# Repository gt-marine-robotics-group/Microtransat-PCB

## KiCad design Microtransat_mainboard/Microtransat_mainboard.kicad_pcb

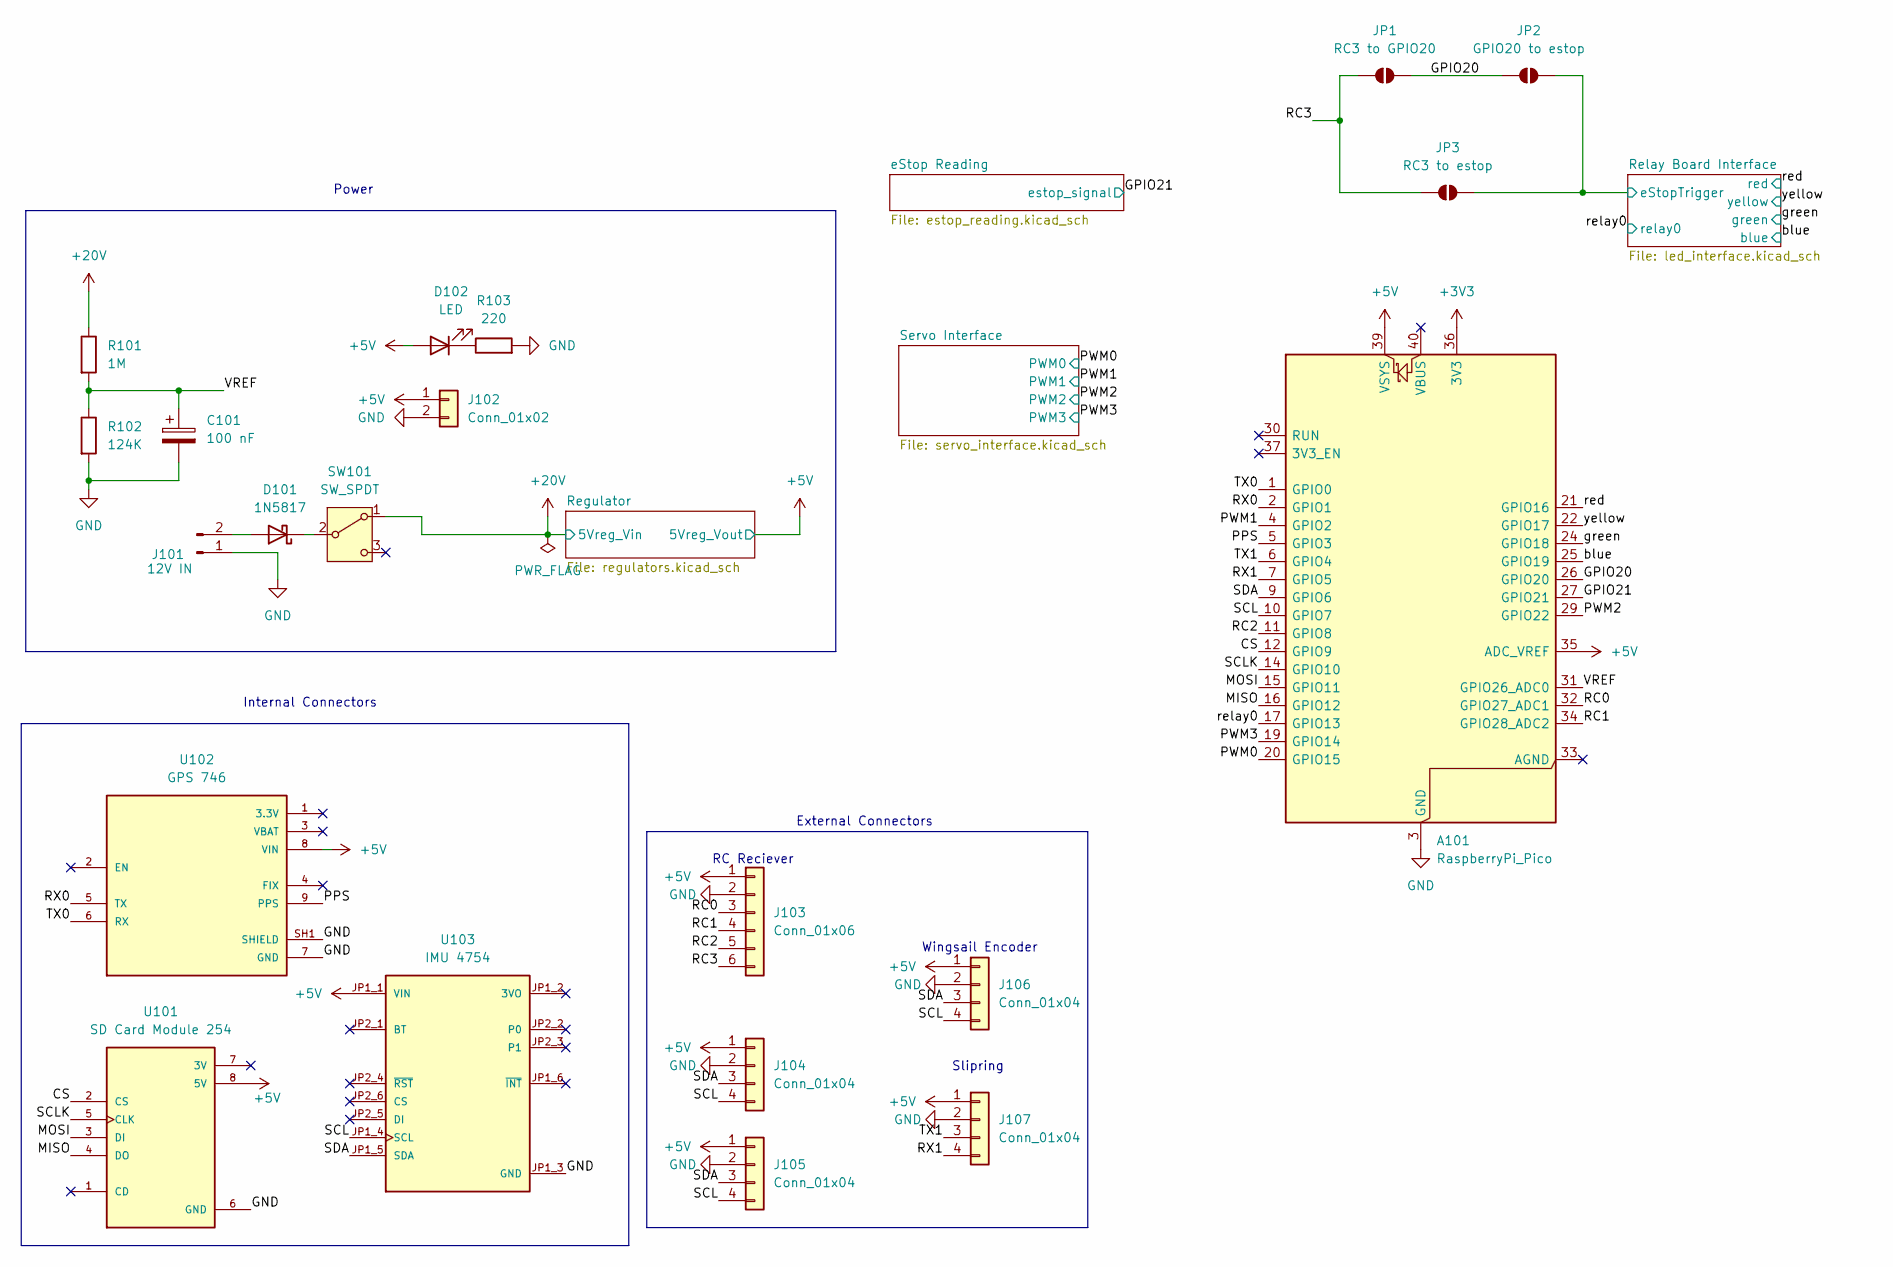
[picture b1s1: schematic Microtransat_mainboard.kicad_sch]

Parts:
A101: RaspberryPi_Pico; RaspberryPi_Pico_Common_Unspecified
C101: 100 nF; C_1206_3216Metric_Pad1.33x1.80mm_HandSolder
D101: 1N5817; D_DO-41_SOD81_P10.16mm_Horizontal
D102: LED; LED_1206_3216Metric_Pad1.42x1.75mm_HandSolder
J101: 12V IN; AMASS_XT30PW-M_1x02_P2.50mm_Horizontal
J102: Conn_01x02; JST_XH_B2B-XH-A_1x02_P2.50mm_Vertical
J103: Conn_01x06; JST_XH_B6B-XH-A_1x06_P2.50mm_Vertical
J104, J105, J106, J107: Conn_01x04; JST_XH_B4B-XH-A_1x04_P2.50mm_Vertical
JP1: RC3 to GPIO20; SolderJumper-2_P1.3mm_Open_RoundedPad1.0x1.5mm
JP2: GPIO20 to estop; SolderJumper-2_P1.3mm_Open_RoundedPad1.0x1.5mm
JP3: RC3 to estop; SolderJumper-2_P1.3mm_Open_RoundedPad1.0x1.5mm
R101: 1M; R_1206_3216Metric_Pad1.30x1.75mm_HandSolder
R102: 124K; R_1206_3216Metric_Pad1.30x1.75mm_HandSolder
R103: 220; R_1206_3216Metric_Pad1.30x1.75mm_HandSolder
SW101: SW_SPDT; SW_EG1218
U101: SD Card Module 254; MODULE_254; PARTREV Jul 31, 2013; DigiKey_Part_Number 1528-1462-ND
U102: GPS 746; XCVR_746; PARTREV 2022-12-01; DigiKey_Part_Number 1528-1153-ND
U103: IMU 4754; MODULE_4754; PARTREV 2021-03-16; DigiKey_Part_Number 1528-4754-ND

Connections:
+3V3: A101.36 (3V3); also elsewhere on the board
+5V: A101.35 (ADC_VREF), A101.39 (VSYS), D102.2 (A), J102.1, J103.1, J104.1, J105.1, J106.1, J107.1, U101.8 (5V), U102.8 (VIN), U103.JP1_1 (VIN); also elsewhere on the board
+20V: R101.1, SW101.1 (A); also elsewhere on the board
/CS: A101.12 (GPIO9), U101.2 (CS)
/GPIO20: A101.26 (GPIO20), JP1.2 (B), JP2.1 (A)
/GPIO21: A101.27 (GPIO21); also elsewhere on the board
/MISO: A101.16 (GPIO12), U101.4 (DO)
/MOSI: A101.15 (GPIO11), U101.3 (DI)
/PPS: A101.5 (GPIO3), U102.9 (PPS)
/PWM0: A101.20 (GPIO15); also elsewhere on the board
/PWM1: A101.4 (GPIO2); also elsewhere on the board
/PWM2: A101.29 (GPIO22); also elsewhere on the board
/PWM3: A101.19 (GPIO14); also elsewhere on the board
/RC0: A101.32 (GPIO27_ADC1), J103.3
/RC1: A101.34 (GPIO28_ADC2), J103.4
/RC2: A101.11 (GPIO8), J103.5
/RC3: J103.6, JP1.1 (A), JP3.1 (A)
/RX0: A101.2 (GPIO1), U102.5 (TX)
/RX1: A101.7 (GPIO5), J107.4
/Relay Board Interface/eStopTrigger: JP2.2 (B), JP3.2 (B); also elsewhere on the board
/SCL: A101.10 (GPIO7), J104.4, J105.4, J106.4, U103.JP1_4 (SCL)
/SCLK: A101.14 (GPIO10), U101.5 (CLK)
/SDA: A101.9 (GPIO6), J104.3, J105.3, J106.3, U103.JP1_5 (SDA)
/TX0: A101.1 (GPIO0), U102.6 (RX)
/TX1: A101.6 (GPIO4), J107.3
/VREF: A101.31 (GPIO26_ADC0), C101.1, R101.2, R102.1
/blue: A101.25 (GPIO19); also elsewhere on the board
/green: A101.24 (GPIO18); also elsewhere on the board
/red: A101.21 (GPIO16); also elsewhere on the board
/relay0: A101.17 (GPIO13); also elsewhere on the board
/yellow: A101.22 (GPIO17); also elsewhere on the board
GND: A101.3 (GND), A101.8 (GND), A101.13 (GND), A101.18 (GND), A101.23 (GND), A101.28 (GND), A101.38 (GND), C101.2, J101.1, J102.2, J103.2, J104.2, J105.2, J106.2, J107.2, R102.2, R103.2, U101.6 (GND), U102.7 (GND), U102.SH1 (SHIELD), U102.SH2 (SHIELD), U103.JP1_3 (GND); also elsewhere on the board
unnamed: D101.2 (A), J101.2
unnamed: D101.1 (K), SW101.2 (B)
unnamed: D102.1 (K), R103.1

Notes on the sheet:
Wingsail Encoder
Internal Connectors
Power
Slipring
RC Reciever
External Connectors

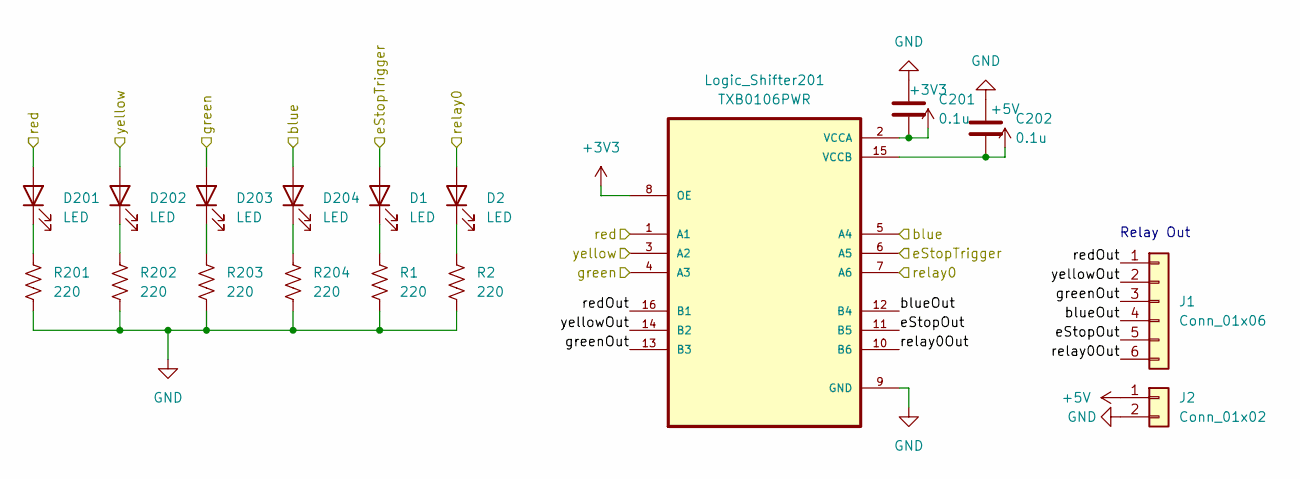
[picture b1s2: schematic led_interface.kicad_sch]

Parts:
C201, C202: 0.1u; C_1206_3216Metric_Pad1.33x1.80mm_HandSolder
D1, D2, D201, D202, D203, D204: LED; LED_1206_3216Metric_Pad1.42x1.75mm_HandSolder
J1: Conn_01x06; JST_XH_B6B-XH-A_1x06_P2.50mm_Vertical
J2: Conn_01x02; JST_XH_B2B-XH-A_1x02_P2.50mm_Vertical
Logic_Shifter201: TXB0106PWR; SOP65P640X120-16N
R1, R2, R201, R202, R203, R204: 220; R_1206_3216Metric_Pad1.30x1.75mm_HandSolder

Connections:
+3V3: C201.1, Logic_Shifter201.2 (VCCA), Logic_Shifter201.8 (OE); also elsewhere on the board
+5V: C202.1, J2.1, Logic_Shifter201.15 (VCCB); also elsewhere on the board
/Relay Board Interface/blueOut: J1.4, Logic_Shifter201.12 (B4)
/Relay Board Interface/eStopOut: J1.5, Logic_Shifter201.11 (B5)
/Relay Board Interface/eStopTrigger: D1.2 (A), Logic_Shifter201.6 (A5); also elsewhere on the board
/Relay Board Interface/greenOut: J1.3, Logic_Shifter201.13 (B3)
/Relay Board Interface/redOut: J1.1, Logic_Shifter201.16 (B1)
/Relay Board Interface/relay0Out: J1.6, Logic_Shifter201.10 (B6)
/Relay Board Interface/yellowOut: J1.2, Logic_Shifter201.14 (B2)
/blue: D204.2 (A), Logic_Shifter201.5 (A4); also elsewhere on the board
/green: D203.2 (A), Logic_Shifter201.4 (A3); also elsewhere on the board
/red: D201.2 (A), Logic_Shifter201.1 (A1); also elsewhere on the board
/relay0: D2.2 (A), Logic_Shifter201.7 (A6); also elsewhere on the board
/yellow: D202.2 (A), Logic_Shifter201.3 (A2); also elsewhere on the board
GND: C201.2, C202.2, J2.2, Logic_Shifter201.9 (GND), R1.2, R2.2, R201.2, R202.2, R203.2, R204.2; also elsewhere on the board
unnamed: D1.1 (K), R1.1
unnamed: D2.1 (K), R2.1
unnamed: D201.1 (K), R201.1
unnamed: D202.1 (K), R202.1
unnamed: D203.1 (K), R203.1
unnamed: D204.1 (K), R204.1

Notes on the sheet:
Relay Out

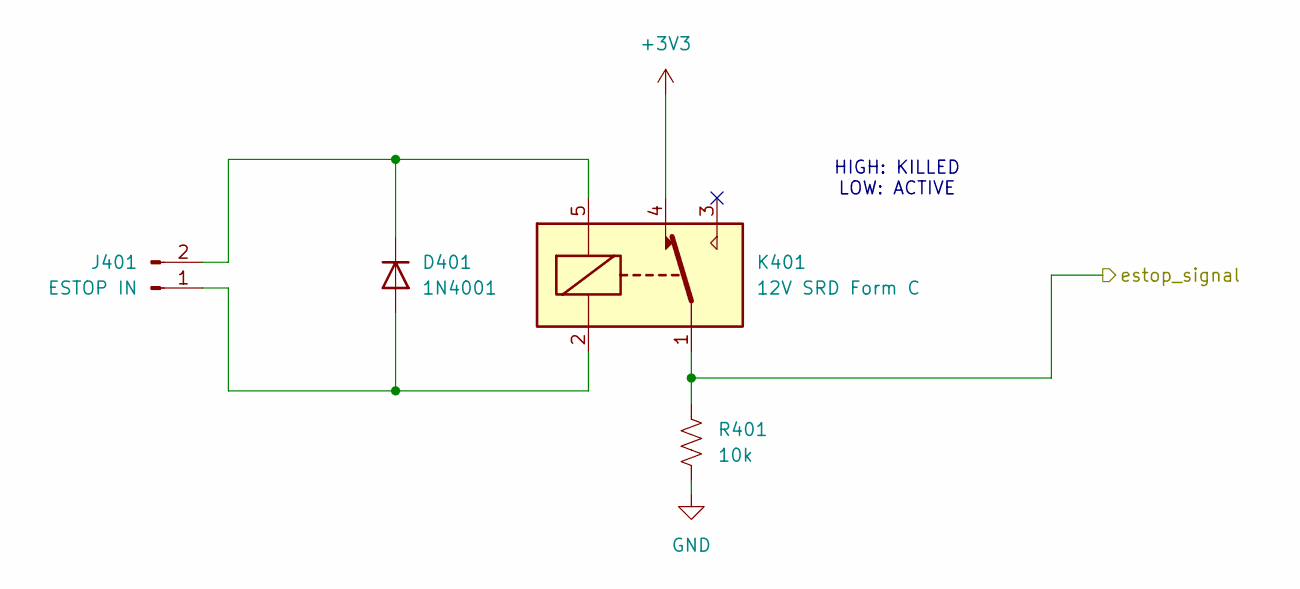
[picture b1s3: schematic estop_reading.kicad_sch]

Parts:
D401: 1N4001; D_DO-41_SOD81_P10.16mm_Horizontal
J401: ESTOP IN; AMASS_XT30PW-M_1x02_P2.50mm_Horizontal
K401: 12V SRD Form C; Relay_SPDT_SANYOU_SRD_Series_Form_C
R401: 10k; R_1206_3216Metric_Pad1.30x1.75mm_HandSolder

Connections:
+3V3: K401.4; also elsewhere on the board
/GPIO21: K401.1, R401.1; also elsewhere on the board
GND: R401.2; also elsewhere on the board
unnamed: D401.2 (A), J401.1, K401.2
unnamed: D401.1 (K), J401.2, K401.5

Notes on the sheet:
HIGH: KILLED LOW: ACTIVE

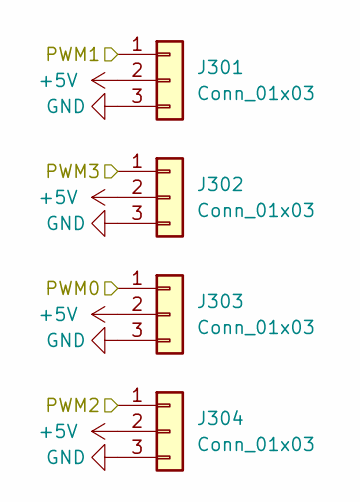
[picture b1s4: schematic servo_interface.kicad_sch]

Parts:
J301, J302, J303, J304: Conn_01x03; JST_XH_B3B-XH-A_1x03_P2.50mm_Vertical

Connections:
+5V: J301.2, J302.2, J303.2, J304.2; also elsewhere on the board
/PWM0: J303.1; also elsewhere on the board
/PWM1: J301.1; also elsewhere on the board
/PWM2: J304.1; also elsewhere on the board
/PWM3: J302.1; also elsewhere on the board
GND: J301.3, J302.3, J303.3, J304.3; also elsewhere on the board

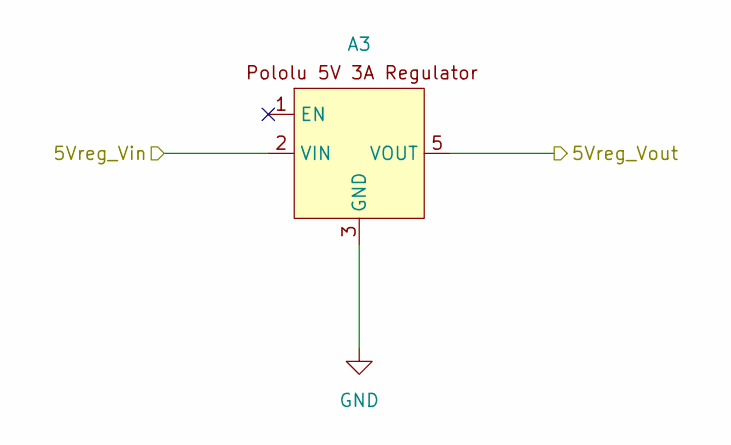
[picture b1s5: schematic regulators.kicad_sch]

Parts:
A3: Pololu 5V 3A Regulator

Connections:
unnamed: A3.3 (GND), A3.4 (GND)

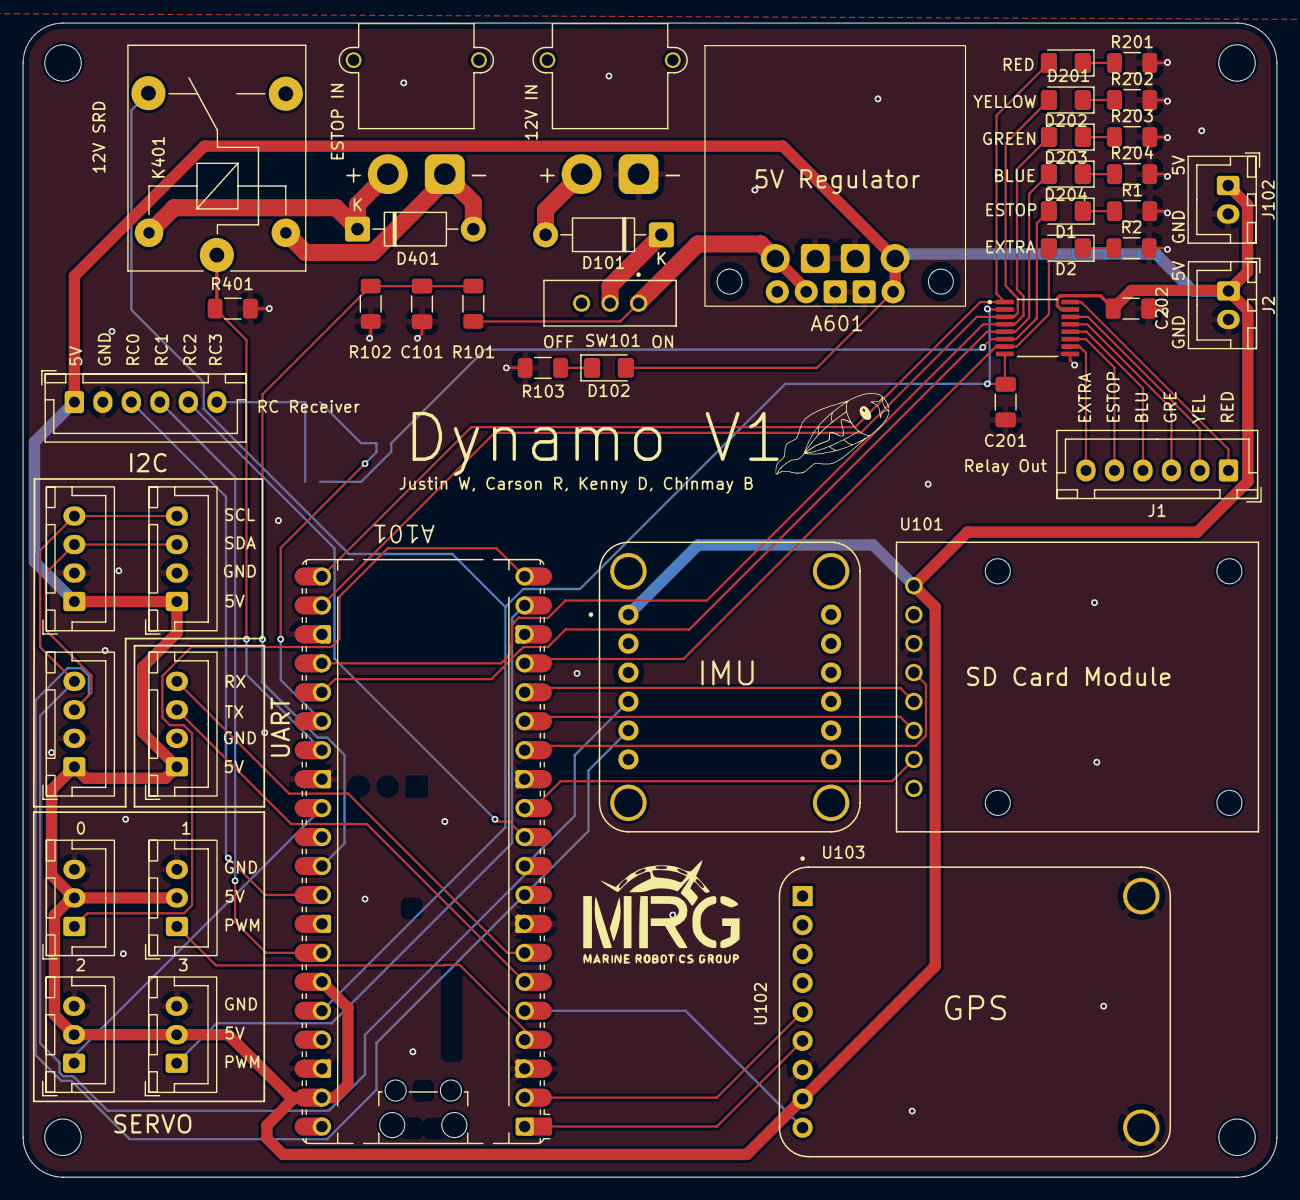
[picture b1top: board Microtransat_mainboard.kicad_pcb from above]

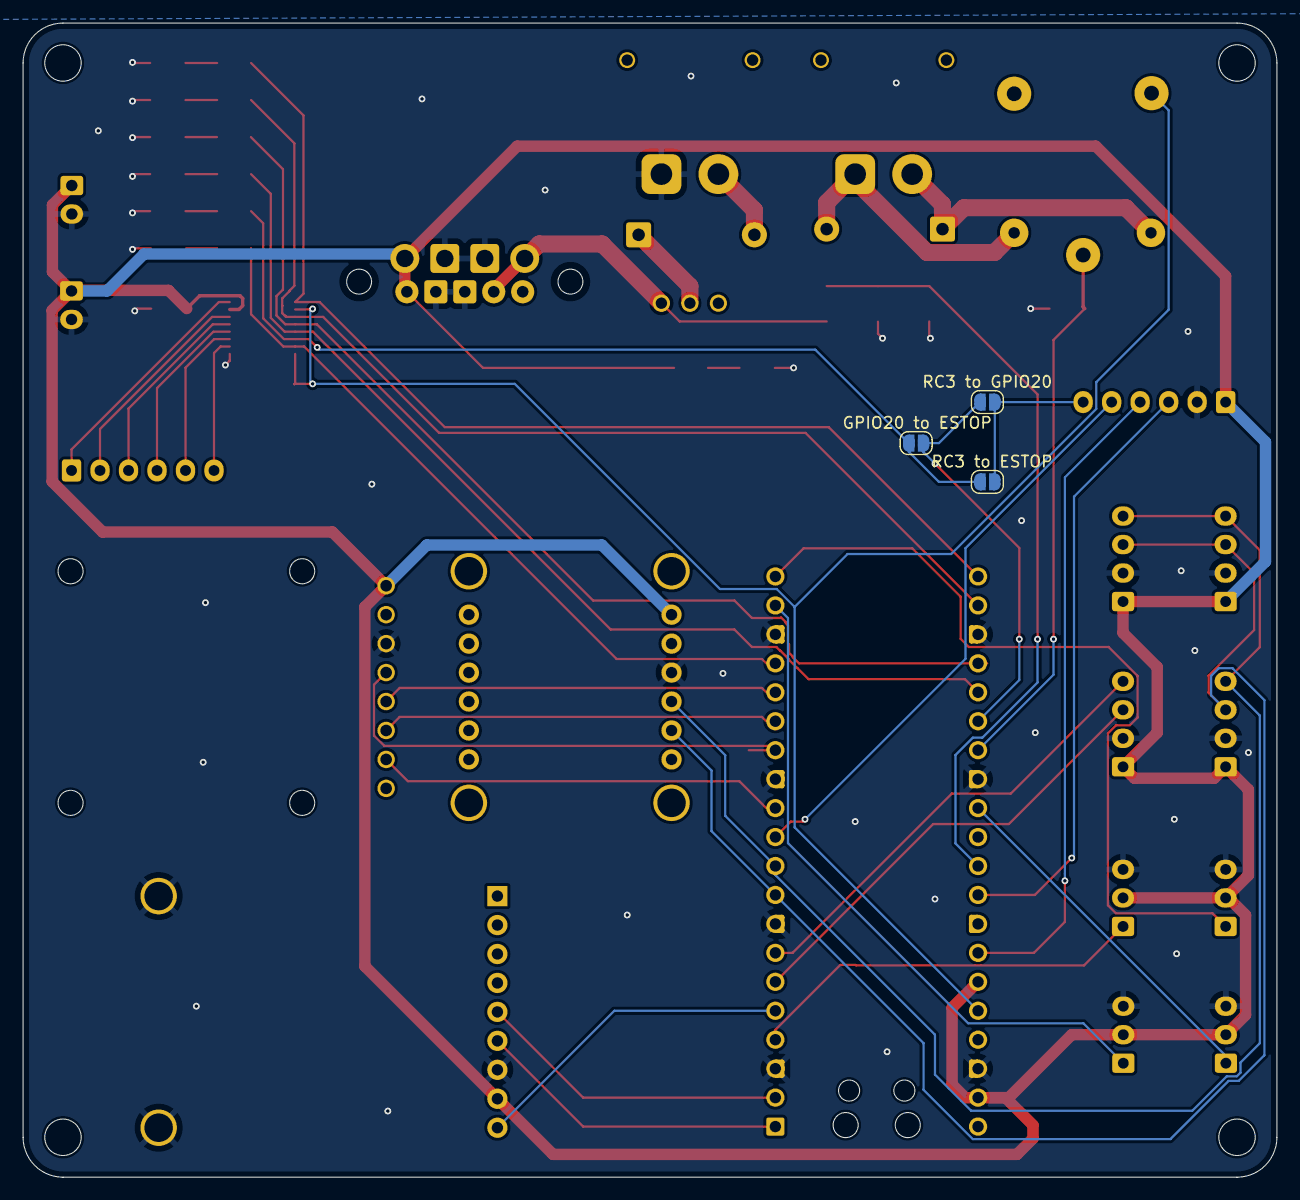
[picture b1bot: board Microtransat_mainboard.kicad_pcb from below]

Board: 2 copper layers, 110.0 x 101.2 mm, 47 parts (3 on the bottom side), 49 nets.

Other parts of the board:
A601: Pololu 5V 3A Regulator

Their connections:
+5V: A601.5 (VOUT); also elsewhere on the board
+20V: A601.2 (VIN); also elsewhere on the board
GND: A601.3 (GND), A601.4 (GND); also elsewhere on the board

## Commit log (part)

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2026-02-07 Added datasheets
2026-02-07 Added in work on overall boat schematic
2026-02-07 Added basic schematic for mainboard
2026-02-19 Added AS5600 mockup
2026-02-21 Removed some old/incorrect stuff
2026-02-23 Some adjustments
2026-02-28 Added SD card footprint
2026-02-28 LM2596 courtyard added
2026-02-28 Moved symbol and footprint into libraries folder
2026-02-28 really moved libraries
2026-02-28 Fixed up mainboard schematic
2026-03-01 Readding footprints for GPS + IMU
2026-03-01 Updated IMU symbol
    V2 -> V3 SPI
2026-03-01 Fixed library paths to project environment variable
2026-03-07 added led and servo interface
2026-03-07 Fixed merge error
2026-03-07 add estop stuff kinda
2026-03-07 Deleting presto board
2026-03-07 Added new IMU to the schematic + new PWM
2026-03-07 Added BNO085 IMU libraries
2026-03-07 Added GPS breakout libraries
2026-03-07 Added SD card breakout libraries
2026-03-07 Stole footprints for RC Switch and Regulator
2026-03-07 Added regulators and updated GPS, IMU, SD Card symbols
2026-03-07 Fixed ERC errors
2026-03-07 Added switch
2026-03-07 Updated footprints
2026-03-07 update resistor
2026-03-07 Started PCB
2026-03-07 Added power connector for raspberry pi
2026-03-13 Added second RC switch for mode pin, added additional relay output, changed IMU to I2C
2026-03-14 moved pcb around
2026-03-14 we did our best...
2026-04-04 routed the traces (maybe?)
2026-04-08 DRC passing
2026-04-08 Fixed RC Receiver pin header
2026-04-09 Updated PCB silkscreen
2026-04-09 Finished silkscreen/outline changes
2026-04-10 Some small changes to silkscreen and component numbers
2026-04-10 Fixed changes from design review
2026-05-19 Exported production files
